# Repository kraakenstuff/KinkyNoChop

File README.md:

# KinkyNoChop
3U Eurorack quad wavefolder based on Befaco's Chopping Kinky.
Status: never finished.

This work is licensed under a Creative Commons Attribution-NonCommercial-ShareAlike 4.0 International License.

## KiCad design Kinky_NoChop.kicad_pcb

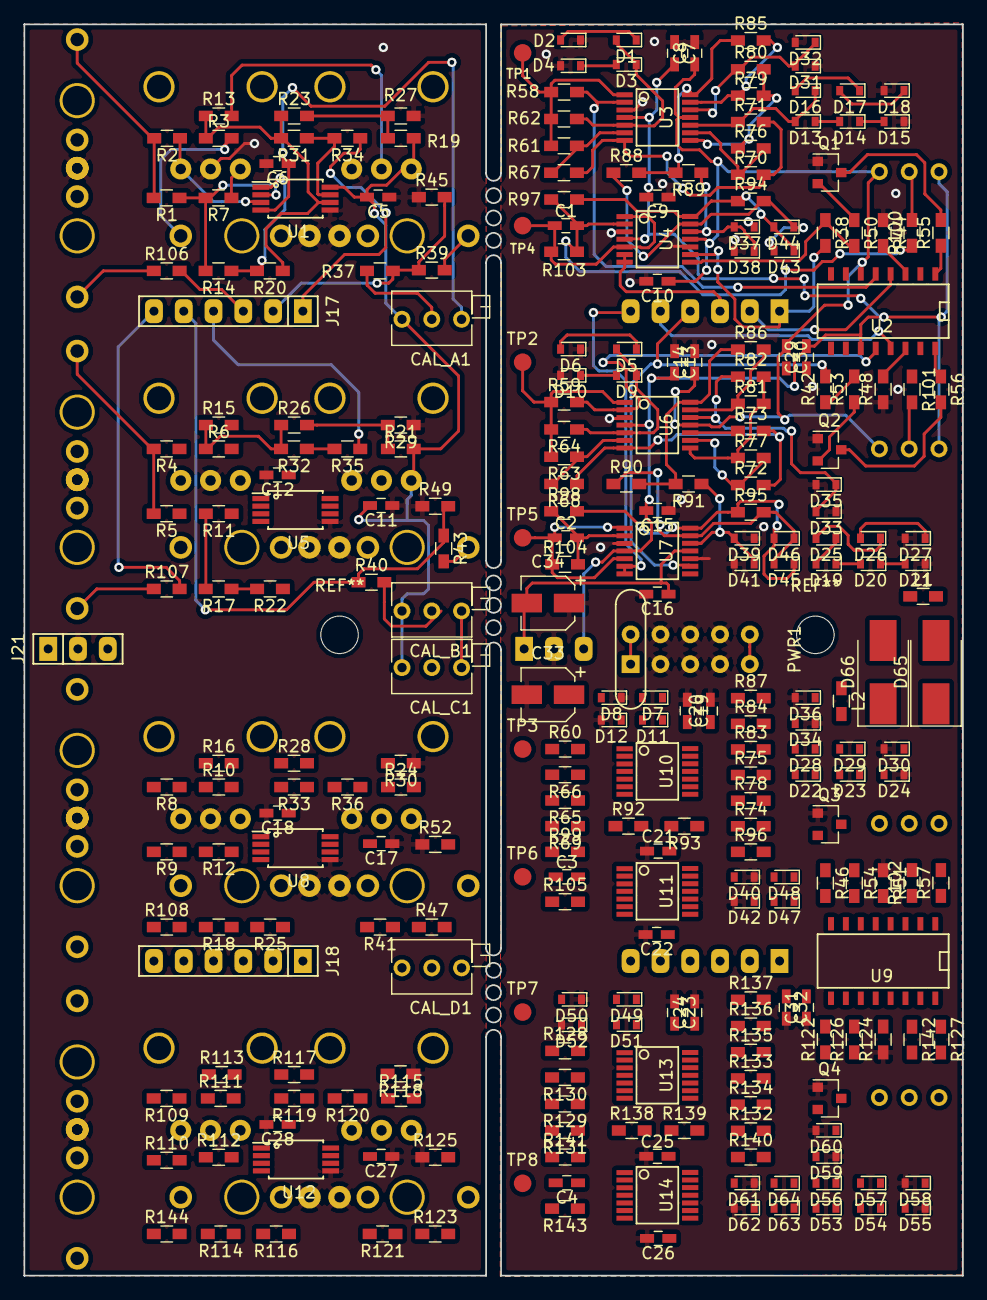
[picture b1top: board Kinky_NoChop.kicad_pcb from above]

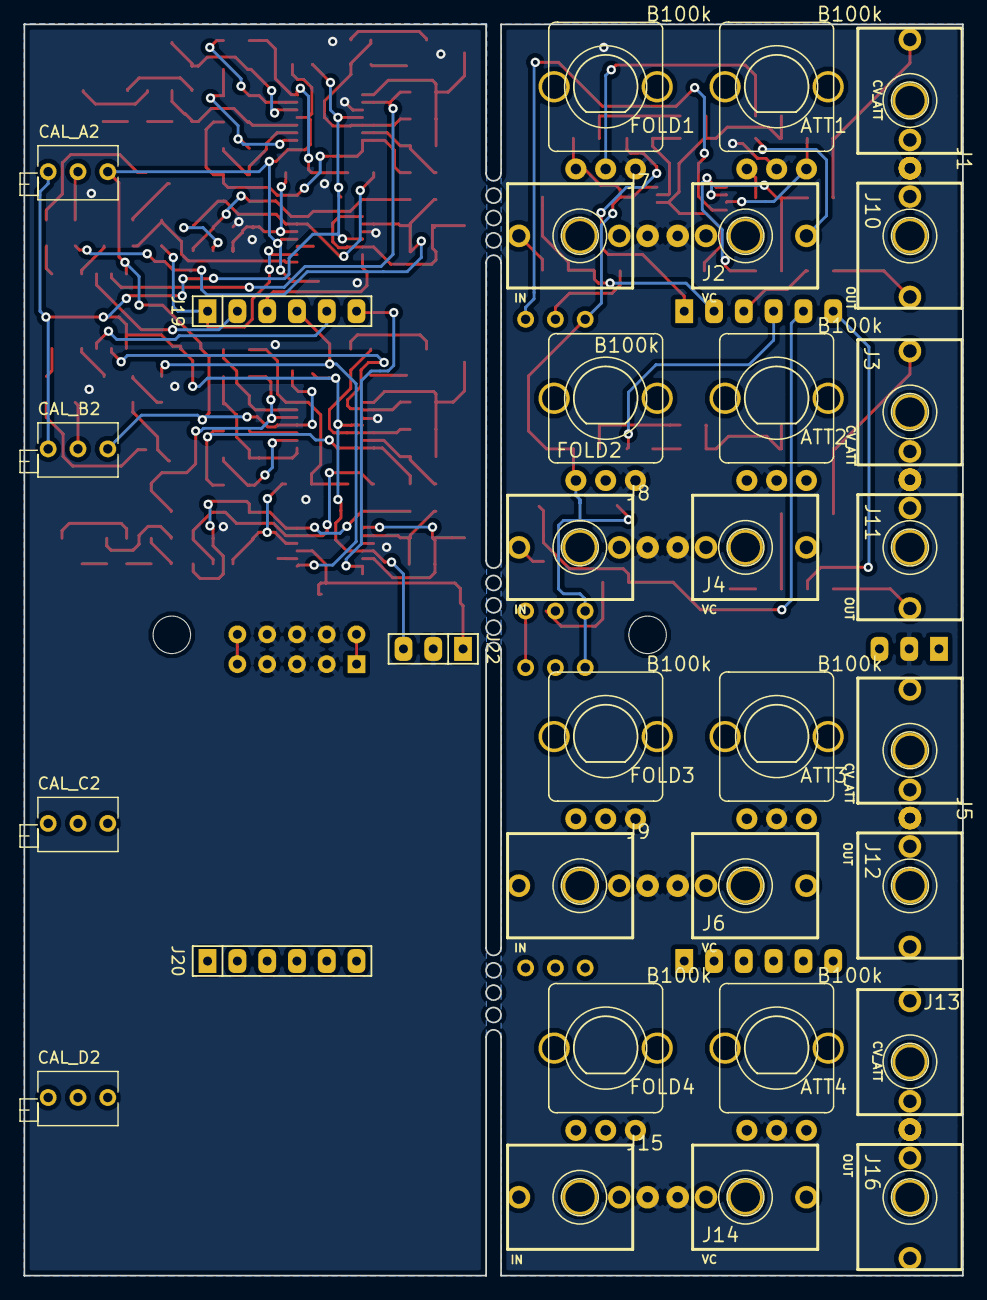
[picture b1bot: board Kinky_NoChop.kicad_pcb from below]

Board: 2 copper layers, 80.0 x 106.7 mm, 311 parts (31 on the bottom side), 183 nets.

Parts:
ATT1, ATT2, ATT3, ATT4: B100k; POT-9MM-ALPHA
C1, C2, C3, C4: 10p; C_0603_HandSoldering
C5, C6, C7, C8, C9, C10, C11, C12, C13, C14, C15, C16, C17, C18, C19, C20, C21, C22, C23, C24, C25, C26, C27, C28, C29, C30, C31, C32: 100n; C_0603_HandSoldering
C33, C34: CP; CP_Elec_4x5.8
CAL_A1, CAL_A2: 10k; Potentiometer_Trimmer_Bourns_3266Z
CAL_B1, CAL_B2: 10k; Potentiometer_Trimmer_Bourns_3266Z
CAL_C1, CAL_C2: 10k; Potentiometer_Trimmer_Bourns_3266Z
CAL_D1, CAL_D2: 10k; Potentiometer_Trimmer_Bourns_3266Z
D1, D2, D3, D4, D5, D6, D7, D8, D9, D10, D11, D12, D13, D14, D15, D16, D17, D18, D19, D20, D21, D22, D23, D24, D25, D26, D27, D28, D29, D30, D31, D32, D33, D34, D35, D36, D37, D38, D39, D40, D41, D42, D43, D44, D45, D46, D47, D48, D49, D50, D51, D52, D53, D54, D55, D56, D57, D58, D59, D60, D61, D62, D63, D64: 1N4148; D_0603
D65, D66: 1N5817; D_SMB_Handsoldering
FOLD1, FOLD2, FOLD3, FOLD4: B100k; POT-9MM-ALPHA
J1, J3, J5, J13: CV_ATT; PJ301M-12
J2, J4, J6, J14: VC; PJ301M-12
J7, J8, J9, J15: IN; PJ301M-12
J10, J11, J12, J16: OUT; PJ301M-12
J17, J18: Ctrl; Header 1x6
J19, J20: Main; Header 1x6
J21: Ctrl; Header 1x3
J22: Main; Header 1x3
L1, L2: Ferrite_Bead; R_0603_HandSoldering
PWR1: EuroHeader10
Q1, Q2, Q3, Q4: MMBT3906; SOT-23
R1, R2, R3, R4, R5, R6, R8, R9, R10, R14, R17, R18, R20, R22, R25, R27, R29, R30, R31, R32, R33, R38, R39, R42, R43, R46, R47, R58, R59, R60, R61, R62, R63, R64, R65, R66, R67, R68, R69, R70, R71, R72, R73, R74, R75, R76, R77, R78, R79, R80, R81, R82, R83, R84, R85, R86, R87, R88, R89, R90, R91, R92, R93, R94, R95, R96, R109, R110, R111, R114, R116, R118, R119, R122, R123, R128, R129, R130, R131, R132, R133, R134, R135, R136, R137, R138, R139, R140: 100k; R_0603_HandSoldering
R7, R11, R12, R112: 43k; R_0603_HandSoldering
R13, R15, R16, R113: 120k; R_0603_HandSoldering
R19, R21, R24, R115: 82k; R_0603_HandSoldering
R23, R26, R28, R37, R40, R41, R100, R101, R102, R117, R121, R142: 1M; R_0603_HandSoldering
R34, R35, R36, R120: 200k; R_0603_HandSoldering
R44, R45, R48, R49, R51, R52, R124, R125: 560R; R_0603_HandSoldering
R50, R53, R54, R126: 30k; R_0603_HandSoldering
R55, R56, R57, R127: 20k; R_0603_HandSoldering
R97, R98, R99, R141: 10k; R_0603_HandSoldering
R103, R104, R105, R143: 300k; R_0603_HandSoldering
R106, R107, R108, R144: 1k; R_0603_HandSoldering
TP1: TP_A1; Measurement_Point_Round-SMD-Pad_Small
TP2: TP_B1; Measurement_Point_Round-SMD-Pad_Small
TP3, TP7: TP_C1; Measurement_Point_Round-SMD-Pad_Small
TP4: TP_A2; Measurement_Point_Round-SMD-Pad_Small
TP5: TP_B2; Measurement_Point_Round-SMD-Pad_Small
TP6, TP8: TP_C2; Measurement_Point_Round-SMD-Pad_Small
U1, U5, U8, U12: TL072; TSSOP-8_4.4x3mm_Pitch0.65mm
U2, U9: LM13700; SO-16-N
U3, U4, U6, U7, U10, U11, U13, U14: TL074; SSOP-14

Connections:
+12V: C5.2, C7.2, C9.2, C11.2, C13.2, C15.2, C17.2, C19.2, C21.2, C23.2, C25.2, C27.2, C29.2, C31.2, C33.1, CAL_A1.1, CAL_A2.3, CAL_B1.1, CAL_B2.3, CAL_C1.1, CAL_C2.3, CAL_D1.1, CAL_D2.3, D65.1, FOLD1.1, FOLD2.1, FOLD3.1, FOLD4.1, J21.3, J22.3, R19.2, R21.2, R24.2, R115.2, U1.8, U2.11, U3.4, U4.4, U5.8, U6.4, U7.4, U8.8, U9.11, U10.4, U11.4, U12.8, U13.4, U14.4
-12V: C6.1, C8.1, C10.1, C12.1, C14.1, C16.1, C18.1, C20.1, C22.1, C24.1, C26.1, C28.1, C30.1, C32.1, C34.2, CAL_A1.3, CAL_A2.1, CAL_B1.3, CAL_B2.1, CAL_C1.3, CAL_C2.1, CAL_D1.3, CAL_D2.1, D66.2, J21.1, J22.1, U1.4, U2.6, U3.11, U4.11, U5.4, U6.11, U7.11, U8.4, U9.6, U10.11, U11.11, U12.4, U13.11, U14.11
A1: J17.1, J19.1, R34.1, R38.2, U4.9
A2: J17.2, J19.2, R37.1, R39.1, R45.2, U2.4
A3: J17.3, J19.3, R106.2, U4.6, U4.7
B1: J17.4, J19.4, R35.1, R42.2, U7.9
B2: J17.5, J19.5, R40.1, R43.1, R49.2, U2.13
B3: J17.6, J19.6, R107.2, U7.6, U7.7
C1: J18.1, J20.1, R36.1, R46.2, U11.9
C2: J18.2, J20.2, R41.1, R47.1, R52.2, U9.4
C3: J18.3, J20.3, R108.2, U11.6, U11.7
D1: J18.4, J20.4, R120.1, R122.2, U14.9
D2: J18.5, J20.5, R121.1, R123.1, R125.2, U9.13
D3: J18.6, J20.6, R144.2, U14.6, U14.7
GND: ATT1.2, ATT2.2, ATT3.2, ATT4.2, C5.1, C6.2, C7.1, C8.2, C9.1, C10.2, C11.1, C12.2, C13.1, C14.2, C15.1, C16.2, C17.1, C18.2, C19.1, C20.2, C21.1, C22.2, C23.1, C24.2, C25.1, C26.2, C27.1, C28.2, C29.1, C30.2, C31.1, C32.2, C33.2, C34.1, D2.1, D4.2, D6.1, D8.1, D10.2, D12.2, D15.1, D18.2, D21.1, D24.1, D27.2, D30.2, D31.1, D32.2, D33.1, D34.1, D35.2, D36.2, D37.1, D38.2, D39.1, D40.1, D41.2, D42.2, D50.1, D52.2, D55.1, D58.2, D59.1, D60.2, D61.1, D62.2, FOLD1.3, FOLD2.3, FOLD3.3, FOLD4.3, J1.1, J2.1, J3.1, J4.1, J5.1, J6.1, J7.1, J8.1, J9.1, J10.1, J11.1, J12.1, J13.1, J14.1, J15.1, J16.1, J21.2, J22.2, PWR1.3, PWR1.4, PWR1.5, PWR1.6, PWR1.7, PWR1.8, Q1.1, Q2.1, Q3.1, Q4.1, R27.1, R29.1, R30.1, R44.1, R45.1, R48.1, R49.1, R51.1, R52.1, R118.1, R124.1, R125.1, U1.5, U3.3, U4.3, U4.10, U5.5, U6.3, U7.3, U7.10, U8.5, U10.3, U11.3, U11.10, U12.5, U13.3, U14.3, U14.10
unnamed: ATT1.1, R7.1
unnamed: ATT1.3, R2.1, U1.3
unnamed: ATT2.1, R11.1
unnamed: ATT2.3, R5.1, U5.3
unnamed: ATT3.1, R12.1
unnamed: ATT3.3, R9.1, U8.3
unnamed: ATT4.1, R112.1
unnamed: ATT4.3, R110.1, U12.3
unnamed: C1.1, R103.1, TP4.1, U4.1, U4.5
unnamed: C1.2, R97.1, R100.1, R103.2, U4.2
unnamed: C2.1, R104.1, TP5.1, U7.1, U7.5
unnamed: C2.2, R98.1, R101.1, R104.2, U7.2
unnamed: C3.1, R105.1, TP6.1, U11.1, U11.5
unnamed: C3.2, R99.1, R102.1, R105.2, U11.2
unnamed: C4.1, R143.1, TP8.1, U14.1, U14.5
unnamed: C4.2, R141.1, R142.1, R143.2, U14.2
unnamed: CAL_A1.2, R37.2
unnamed: CAL_A2.2, R100.2
unnamed: CAL_B1.2, R40.2
unnamed: CAL_B2.2, R101.2
unnamed: CAL_C1.2, R41.2
unnamed: CAL_C2.2, R102.2
unnamed: CAL_D1.2, R121.2
unnamed: CAL_D2.2, R142.2
unnamed: D1.1, D2.2
unnamed: D1.2, D3.1, R62.1, U3.5
unnamed: D3.2, D4.1
unnamed: D5.1, D6.2
unnamed: D5.2, D9.1, R64.1, U6.5
unnamed: D7.1, D8.2
unnamed: D9.2, D10.1
unnamed: D7.2, D11.1, R66.1, U10.5
unnamed: D11.2, D12.1
unnamed: D13.1, D14.2
unnamed: D13.2, D16.1, R71.1, U3.10
unnamed: D14.1, D15.2
unnamed: D16.2, D17.1
unnamed: D17.2, D18.1
unnamed: D19.1, D20.2
unnamed: D19.2, D25.1, R73.1, U6.10
unnamed: D20.1, D21.2
unnamed: D22.1, D23.2
unnamed: D22.2, D28.1, R75.1, U10.10
unnamed: D23.1, D24.2
unnamed: D25.2, D26.1
unnamed: D26.2, D27.1
unnamed: D28.2, D29.1
unnamed: D29.2, D30.1
unnamed: D31.2, D32.1, R80.1, U3.12
unnamed: D33.2, D35.1, R82.1, U6.12
unnamed: D34.2, D36.1, R84.1, U10.12
unnamed: D37.2, D38.1, R89.1, U4.12
unnamed: D39.2, D41.1, R91.1, U7.12
unnamed: D40.2, D42.1, R93.1, U11.12
unnamed: D43.1, D44.2, R94.1, R97.2, U4.14
unnamed: D43.2, D44.1, R88.1, R94.2, U4.13
unnamed: D45.1, D46.2, R95.1, R98.2, U7.14
unnamed: D45.2, D46.1, R90.1, R95.2, U7.13
unnamed: D47.1, D48.2, R96.1, R99.2, U11.14
unnamed: D47.2, D48.1, R92.1, R96.2, U11.13
unnamed: D49.1, D50.2
unnamed: D49.2, D51.1, R130.1, U13.5
unnamed: D51.2, D52.1
unnamed: D53.1, D54.2
unnamed: D53.2, D56.1, R133.1, U13.10
unnamed: D54.1, D55.2
unnamed: D56.2, D57.1
unnamed: D57.2, D58.1
unnamed: D59.2, D60.1, R136.1, U13.12
unnamed: D61.2, D62.1, R139.1, U14.12
unnamed: D63.1, D64.2, R140.1, R141.2, U14.14
unnamed: D63.2, D64.1, R138.1, R140.2, U14.13
unnamed: D65.2, L1.2
unnamed: D66.1, L2.2
unnamed: FOLD1.2, R13.2
unnamed: FOLD2.2, R15.2
unnamed: FOLD3.2, R16.2
unnamed: FOLD4.2, R113.2
unnamed: J1.3, R1.2, R2.2
unnamed: J2.3, R3.2
unnamed: J3.3, R4.2, R5.2
unnamed: J4.3, R6.2
unnamed: J5.3, R8.2, R9.2
unnamed: J6.3, R10.2
unnamed: J7.3, R39.2
unnamed: J8.3, R43.2
unnamed: J9.3, R47.2
unnamed: J10.3, R106.1
unnamed: J11.3, R107.1
unnamed: J12.3, R108.1
unnamed: J13.3, R109.2, R110.2
unnamed: J14.3, R111.2
unnamed: J15.3, R123.2
unnamed: J16.3, R144.1
unnamed: L1.1, PWR1.1, PWR1.2
unnamed: L2.1, PWR1.9, PWR1.10
unnamed: Q1.2, R50.1
unnamed: Q1.3, R55.2
unnamed: Q2.2, R53.1
unnamed: Q2.3, R56.2
unnamed: Q3.2, R54.1
unnamed: Q3.3, R57.2
unnamed: Q4.2, R126.1
unnamed: Q4.3, R127.2
unnamed: R1.1, R7.2, R14.2, U1.2
unnamed: R10.1, R16.1, R25.1, R28.1, R33.2, U8.6
unnamed: R4.1, R11.2, R17.2, U5.2
unnamed: R8.1, R12.2, R18.2, U8.2
unnamed: R3.1, R13.1, R20.1, R23.1, R31.2, U1.6
unnamed: R14.1, R20.2, U1.1
unnamed: R6.1, R15.1, R22.1, R26.1, R32.2, U5.6
unnamed: R17.1, R22.2, U5.1
unnamed: R18.1, R25.2, U8.1
unnamed: R19.1, R23.2, R27.2
unnamed: R21.1, R26.2, R29.2
unnamed: R24.1, R28.2, R30.2
unnamed: R31.1, R34.2, U1.7
unnamed: R32.1, R35.2, U5.7
unnamed: R33.1, R36.2, U8.7
unnamed: R38.1, R50.2, U4.8
unnamed: R42.1, R53.2, U7.8
unnamed: R44.2, U2.3
unnamed: R46.1, R54.2, U11.8
unnamed: R48.2, U2.14
unnamed: R51.2, U9.3
unnamed: R55.1, U2.1
unnamed: R56.1, U2.16
unnamed: R57.1, U9.1
unnamed: R58.1, R61.2, R62.2, TP1.1, U3.1
unnamed: R58.2, U2.5, U3.2
unnamed: R59.1, R63.2, R64.2, TP2.1, U6.1
unnamed: R59.2, U2.12, U6.2
unnamed: R60.1, R65.2, R66.2, TP3.1, U10.1
unnamed: R60.2, U9.5, U10.2
unnamed: R61.1, R67.2, U3.6
unnamed: R63.1, R68.2, U6.6
unnamed: R65.1, R69.2, U10.6
unnamed: R67.1, R70.2, R71.2, U3.7
unnamed: R68.1, R72.2, R73.2, U6.7
unnamed: R69.1, R74.2, R75.2, U10.7
unnamed: R70.1, R76.2, U3.9
unnamed: R72.1, R77.2, U6.9
unnamed: R74.1, R78.2, U10.9
unnamed: R76.1, R79.2, R80.2, U3.8
unnamed: R77.1, R81.2, R82.2, U6.8
unnamed: R78.1, R83.2, R84.2, U10.8
unnamed: R79.1, R85.2, U3.13
unnamed: R81.1, R86.2, U6.13
unnamed: R83.1, R87.2, U10.13
unnamed: R85.1, R88.2, R89.2, U3.14
unnamed: R86.1, R90.2, R91.2, U6.14
unnamed: R87.1, R92.2, R93.2, U10.14
unnamed: R109.1, R112.2, R114.2, U12.2
unnamed: R111.1, R113.1, R116.1, R117.1, R119.2, U12.6
unnamed: R114.1, R116.2, U12.1
unnamed: R115.1, R117.2, R118.2
unnamed: R119.1, R120.2, U12.7
unnamed: R122.1, R126.2, U14.8
unnamed: R124.2, U9.14
unnamed: R127.1, U9.16
unnamed: R128.1, R129.2, R130.2, TP7.1, U13.1
unnamed: R128.2, U9.12, U13.2
unnamed: R129.1, R131.2, U13.6
unnamed: R131.1, R132.2, R133.2, U13.7
unnamed: R132.1, R134.2, U13.9
unnamed: R134.1, R135.2, R136.2, U13.8
unnamed: R135.1, R137.2, U13.13
unnamed: R137.1, R138.2, R139.2, U13.14

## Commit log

2018-11-25 Updated README file
2018-11-28 Worked on the second wavefolder
2018-12-02 Started refactoring schematic
